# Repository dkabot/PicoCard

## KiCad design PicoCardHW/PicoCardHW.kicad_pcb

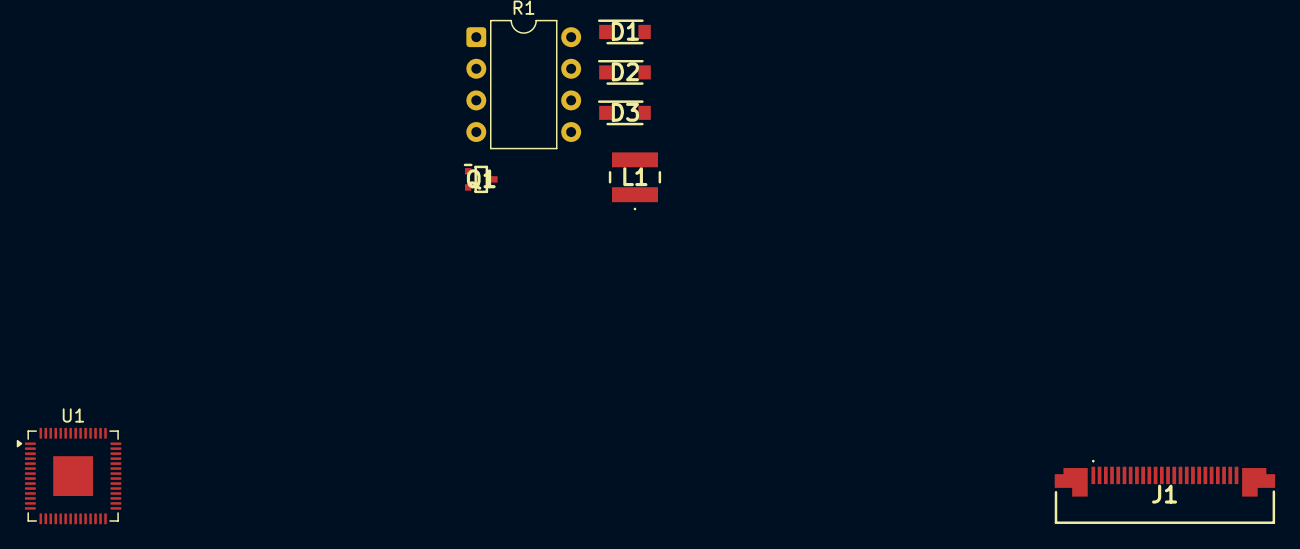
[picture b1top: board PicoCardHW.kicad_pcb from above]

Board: 2 copper layers, 8 parts (0 on the bottom side), 10 nets, no tracks yet.

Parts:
D1, D2, D3: SS2040FL; SODFL3618X108N
J1: SFV24R-1STE1HLF; SFV24R1STE1HLF
L1: 10uH ATNR4010100MT; ATNR4010100MT
Q1: MCH3478-TL-W; SOTFL65P210X90-3N
R1: 0.47Ω; DIP-8_W7.62mm
U1: RP2040; QFN-56-1EP_7x7mm_P0.4mm_EP3.2x3.2mm

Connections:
/FPC2: J1.23, Q1.1 (G)
/FPC3: J1.22, Q1.3 (D), R1.1
/FPC21: D1.1 (K), J1.4
/FPC23: D2.2 (A), J1.2
unnamed: D1.2 (A), L1.2, Q1.2 (S)
unnamed: D2.1 (K), D3.2 (A)
unnamed: U1.23 (DVDD), U1.50 (DVDD)
unnamed: U1.1 (IOVDD), U1.10 (IOVDD), U1.22 (IOVDD), U1.33 (IOVDD), U1.42 (IOVDD), U1.49 (IOVDD)
SCR PWR GND: D3.1 (K), J1.8, J1.17, R1.2
SCR PWR SWITCH: J1.9, J1.10, L1.1
